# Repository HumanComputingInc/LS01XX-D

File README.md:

# LS01XX-D
Daughter board for LS01XX Sharp displays compatible with the KB54 keyboard

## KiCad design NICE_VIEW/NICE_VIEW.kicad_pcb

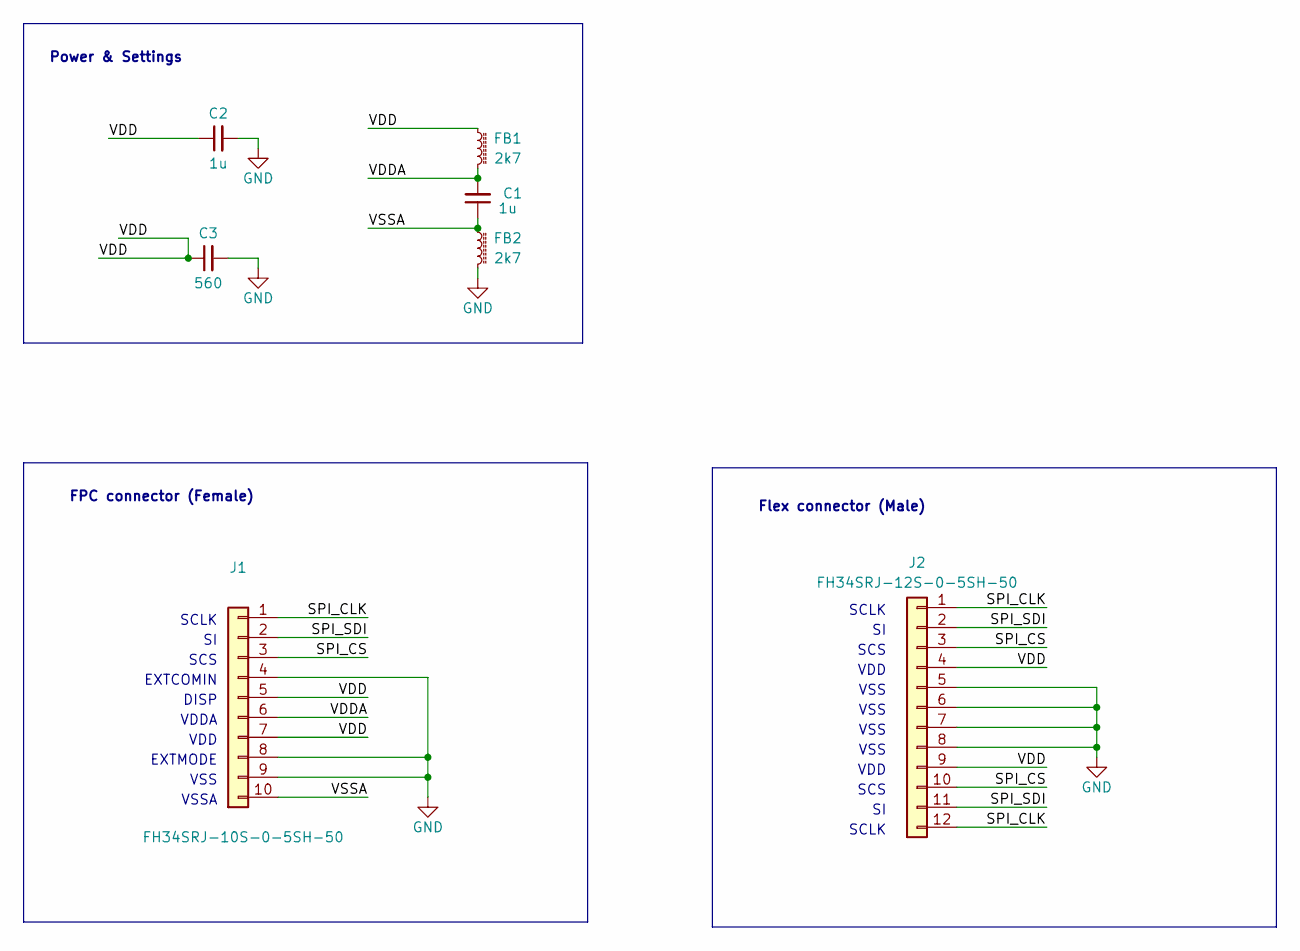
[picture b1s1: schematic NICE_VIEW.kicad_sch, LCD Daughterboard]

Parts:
C1, C2: 1u; C_0402_1005Metric; Part # CL05A105KA5NQNC; LCSC Part # C52923
C3: 560; C_0402_1005Metric; Part # GRM1555C1H561GA01D; LCSC Part # C440169
FB1, FB2: 2k7; L_0805_2012Metric; Part # BLM21BD272SH1L; LCSC Part # C85839
J1: FH34SRJ-10S-0-5SH-50; Conn-FPC_Hirose-FH34SRJ-10S-0-5SH-50; Part # FH34SRJ-10S-0.5SH(50); LCSC Part # C324723
J2: FH34SRJ-12S-0-5SH-50; Conn-FPC_Hirose-FH34SRJ-12S-0-5SH-50; MFR# FH34SRJ-12S-0.5SH(50); LCSC Part # C424659

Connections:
/SPI_CLK: J1.1, J2.1, J2.12
/SPI_CS: J1.3, J2.3, J2.10
/SPI_SDI: J1.2, J2.2, J2.11
/VDD: C2.1, C3.1, FB1.1, J1.5, J1.7, J2.4, J2.9
/VDDA: C1.2, FB1.2, J1.6
/VSSA: C1.1, FB2.1, J1.10
GND: C2.2, C3.2, FB2.2, J1.4, J1.8, J1.9, J2.5, J2.6, J2.7, J2.8

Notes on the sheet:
SCS
VSS
Flex connector (Male)
VSSA
SCLK
EXTCOMIN
VDD
Power & Settings
EXTMODE
FPC connector (Female)
VDDA
DISP

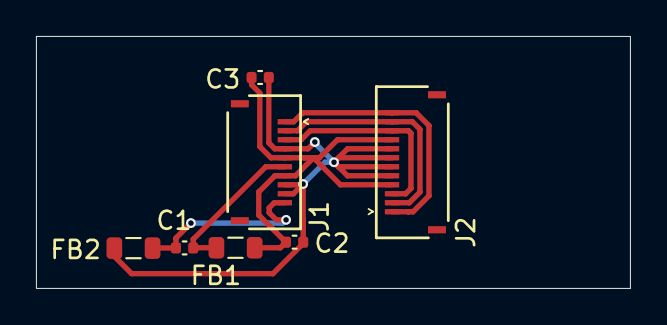
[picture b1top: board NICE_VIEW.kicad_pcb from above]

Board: 2 copper layers, 33.0 x 14.0 mm, 7 parts (0 on the bottom side), 7 nets.

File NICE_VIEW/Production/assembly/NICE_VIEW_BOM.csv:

Designator,Comment,LCSC Part #
C1 C2,1u,C52923
C3,560,C440169
FB1 FB2,2k7,C437409
J1,FH34SRJ-10S-0-5SH-50,C324723
J2,FH34SRJ-12S-0-5SH-50,C424659

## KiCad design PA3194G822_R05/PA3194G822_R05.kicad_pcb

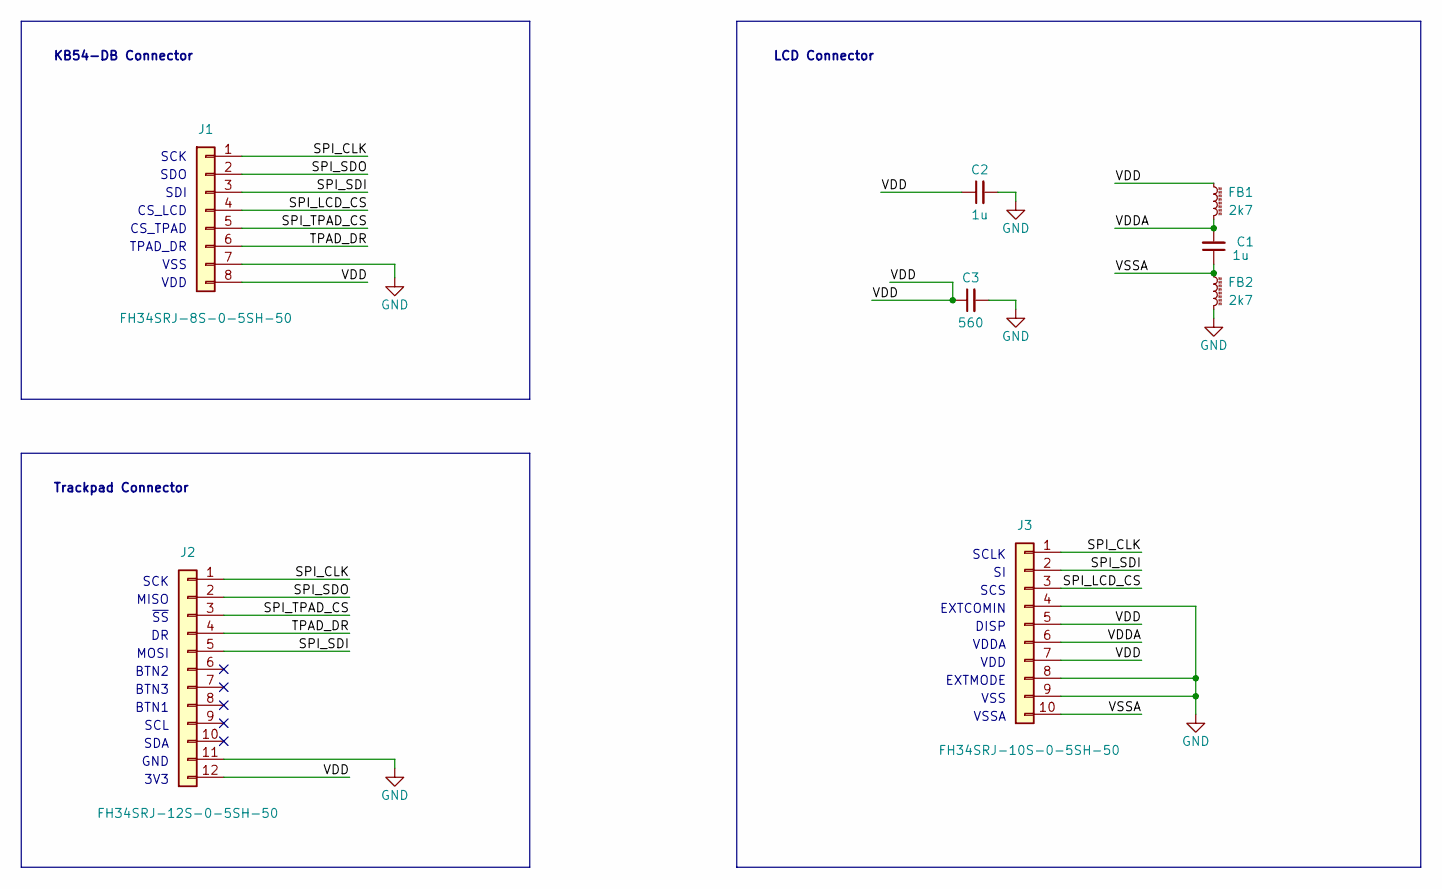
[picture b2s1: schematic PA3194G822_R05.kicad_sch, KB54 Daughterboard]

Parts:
C1, C2: 1u; C_0402_1005Metric; Part # CL05A105KA5NQNC; LCSC Part # C52923
C3: 560; C_0402_1005Metric; Part # GRM1555C1H561GA01D; LCSC Part # C440169
FB1, FB2: 2k7; L_0805_2012Metric; Part # BLM21BD272SH1L; LCSC Part # C437409
J1: FH34SRJ-8S-0-5SH-50; Conn-FPC_Hirose-FH34SRJ-8S-0-5SH-50; Part # FH34SRJ-8S-0.5SH(50); LCSC Part # C88372
J2: FH34SRJ-12S-0-5SH-50; Conn-FPC_Hirose-FH34SRJ-12S-0-5SH-50; Part # FH34SRJ-12S-0.5SH(50); LCSC Part # C424659
J3: FH34SRJ-10S-0-5SH-50; Conn-FPC_Hirose-FH34SRJ-10S-0-5SH-50; Part # FH34SRJ-10S-0.5SH(50); LCSC Part # C324723

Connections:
/SPI_CLK: J1.1, J2.1, J3.1
/SPI_LCD_CS: J1.4, J3.3
/SPI_SDI: J1.3, J2.5, J3.2
/SPI_SDO: J1.2, J2.2
/SPI_TPAD_CS: J1.5, J2.3
/TPAD_DR: J1.6, J2.4
/VDD: C2.1, C3.1, FB1.1, J1.8, J2.12, J3.5, J3.7
/VDDA: C1.2, FB1.2, J3.6
/VSSA: C1.1, FB2.1, J3.10
GND: C2.2, C3.2, FB2.2, J1.7, J2.11, J3.4, J3.8, J3.9

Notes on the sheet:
BTN3
CS_TPAD
Trackpad Connector
MISO
VDD
KB54-DB Connector
VSSA
BTN2
VSS
BTN1
SCLK
SCS
SDI
GND
SCL
SCK
~{SS}
SDA
EXTCOMIN
CS_LCD
MOSI
3V3
LCD Connector
EXTMODE
TPAD_DR
VDDA
DISP
SDO

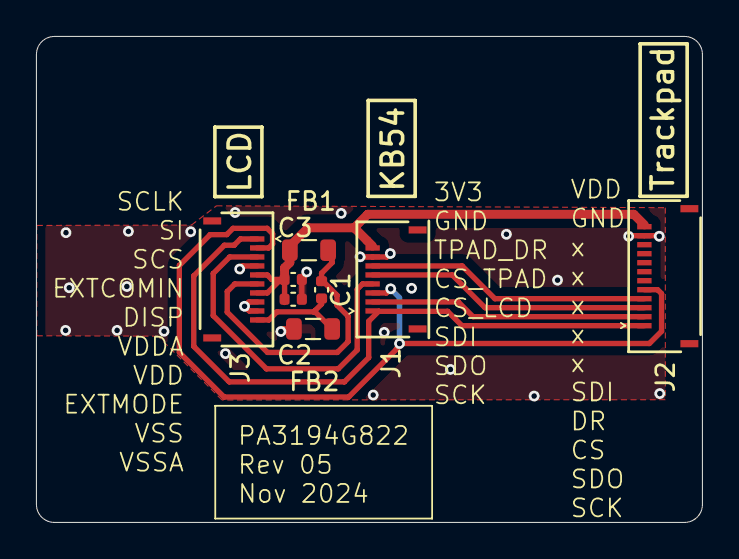
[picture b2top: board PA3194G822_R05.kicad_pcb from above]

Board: 2 copper layers, 37.0 x 27.0 mm, 8 parts (0 on the bottom side), 10 nets.

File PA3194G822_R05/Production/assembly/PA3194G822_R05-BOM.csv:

Comment,Designator,Footprint,LCSC
1u,"C1,C2",Capacitor_SMD:C_0402_1005Metric,C52923
560,C3,Capacitor_SMD:C_0402_1005Metric,C440169
2k7,"FB1,FB2",Inductor_SMD:L_0805_2012Metric,C437409
FH34SRJ-8S-0-5SH-50,J1,Tundra_Connectors:Conn-FPC_Hirose-FH34SRJ-8S-0-5SH-50,C88372
FH34SRJ-12S-0-5SH-50,J2,Tundra_Connectors:Conn-FPC_Hirose-FH34SRJ-12S-0-5SH-50,C424659
FH34SRJ-10S-0-5SH-50,J3,Tundra_Connectors:Conn-FPC_Hirose-FH34SRJ-10S-0-5SH-50,C324723

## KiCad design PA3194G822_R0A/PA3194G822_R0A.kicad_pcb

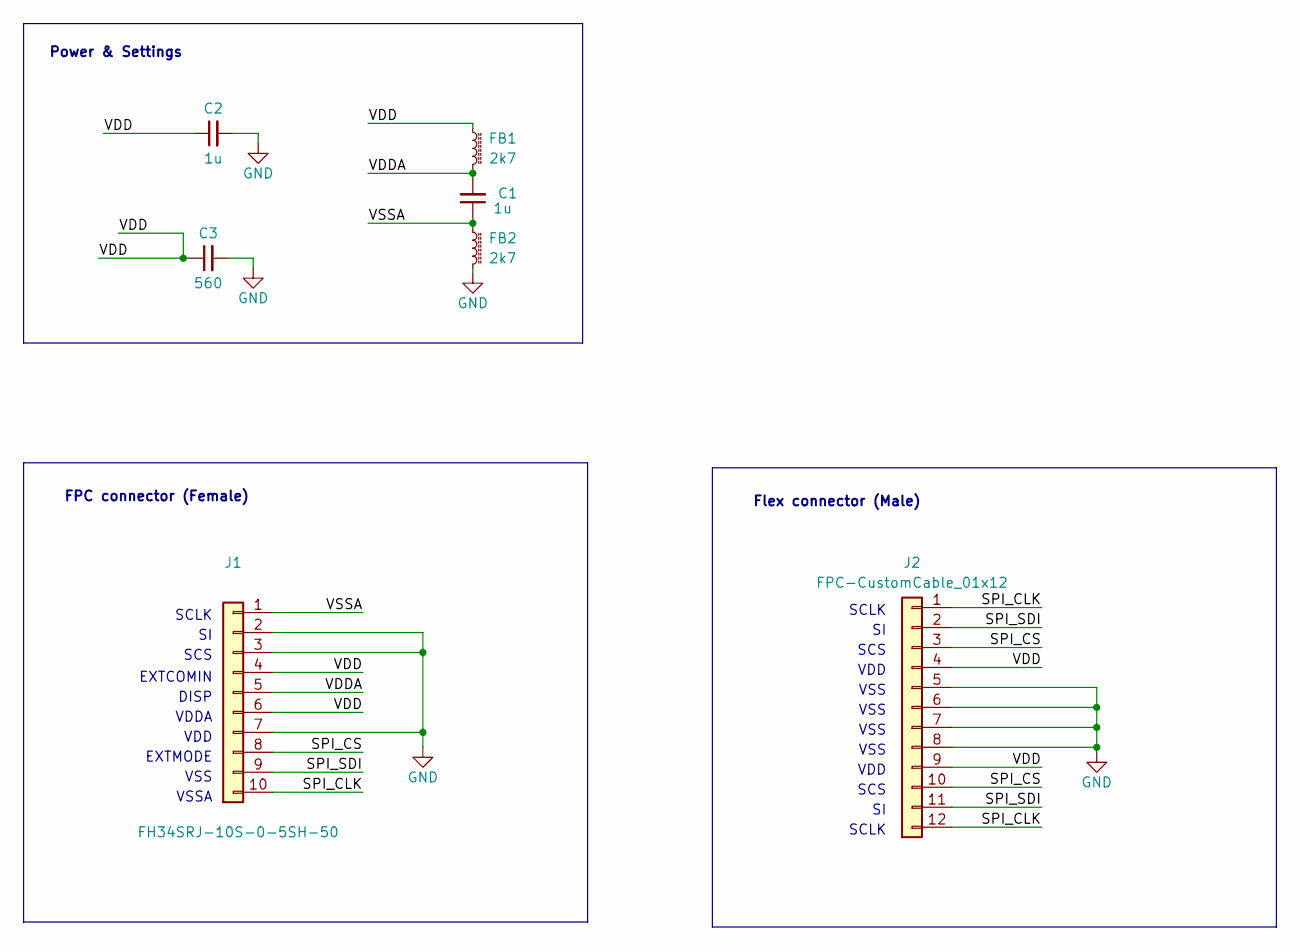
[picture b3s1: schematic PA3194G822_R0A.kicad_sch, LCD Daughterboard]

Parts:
C1, C2: 1u; C_0402_1005Metric; Part # CL05A105KA5NQNC; LCSC Part # C52923
C3: 560; C_0402_1005Metric; Part # GRM1555C1H561GA01D; LCSC Part # C440169
FB1, FB2: 2k7; L_0805_2012Metric; Part # BLM21BD272SH1L; LCSC Part # C437409
J1: FH34SRJ-10S-0-5SH-50; Conn-FPC_Hirose-FH34SRJ-10S-0-5SH-50; Part # FH34SRJ-10S-0.5SH(50); LCSC Part # C324723
J2: FPC-CustomCable_01x12; Conn-FPC-CustomCable_01x12

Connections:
/SPI_CLK: J1.10, J2.1, J2.12
/SPI_CS: J1.8, J2.3, J2.10
/SPI_SDI: J1.9, J2.2, J2.11
/VDD: C2.1, C3.1, FB1.1, J1.4, J1.6, J2.4, J2.9
/VDDA: C1.2, FB1.2, J1.5
/VSSA: C1.1, FB2.1, J1.1
GND: C2.2, C3.2, FB2.2, J1.2, J1.3, J1.7, J2.5, J2.6, J2.7, J2.8

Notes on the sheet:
SCS
VSS
Flex connector (Male)
VSSA
SCLK
EXTCOMIN
VDD
Power & Settings
EXTMODE
FPC connector (Female)
VDDA
DISP

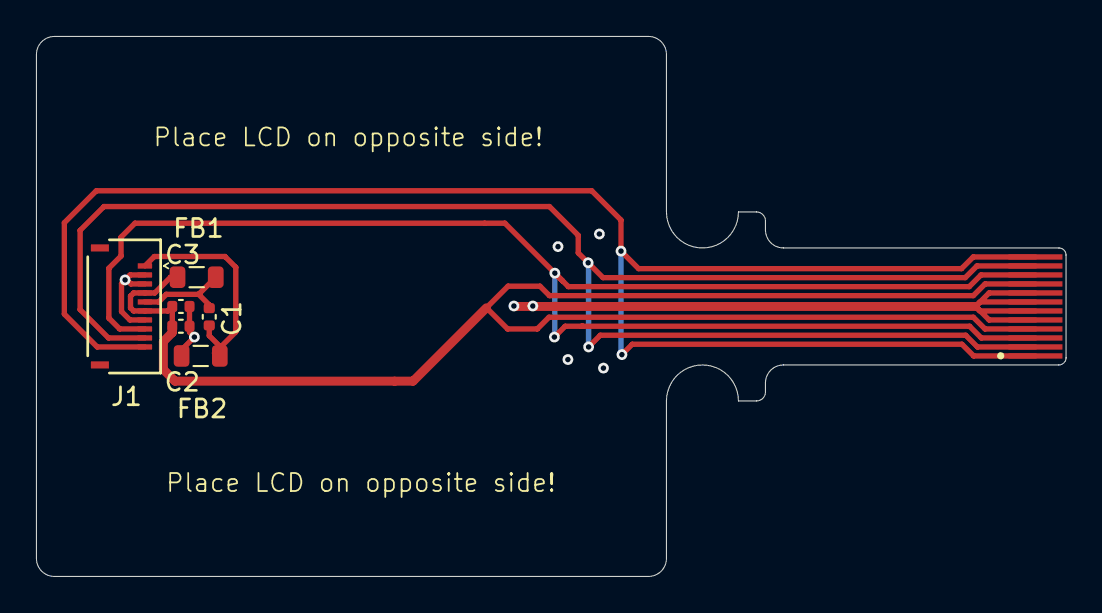
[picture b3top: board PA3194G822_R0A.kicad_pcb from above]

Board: 2 copper layers, 57.2 x 30.0 mm, 7 parts (0 on the bottom side), 7 nets.

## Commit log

2024-05-06 First commit
    Rev01 ready for production
2024-05-06 Moved all ordering info to "Production" folder
2024-07-27 Rev2-4 production
    Ready for production
2024-11-15 Revision 5 ready for production
2025-06-16 Finished the NICE_NANO revision for the KB42S.
